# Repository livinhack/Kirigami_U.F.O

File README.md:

# Kirigami U.F.O.

Kirigami PCB v2 U.F.O.-Edition (inspired by timmit99)

### Since this PCB is a variation of my mod, you can find more helpful information at the link below!

https://github.com/livinhack/Kirigami_U.F.O/assets/91290219/f25b7a1e-6680-43ce-a2c9-361af66e349b

## [Back to Kirigami-PCB](https://github.com/livinhack/Kirigami-PCB)

# Change Log #

## V2.1:
 - The screw terminal moves ~ 3 mm further inwards

## V2:
 - Initial U.F.O. publication

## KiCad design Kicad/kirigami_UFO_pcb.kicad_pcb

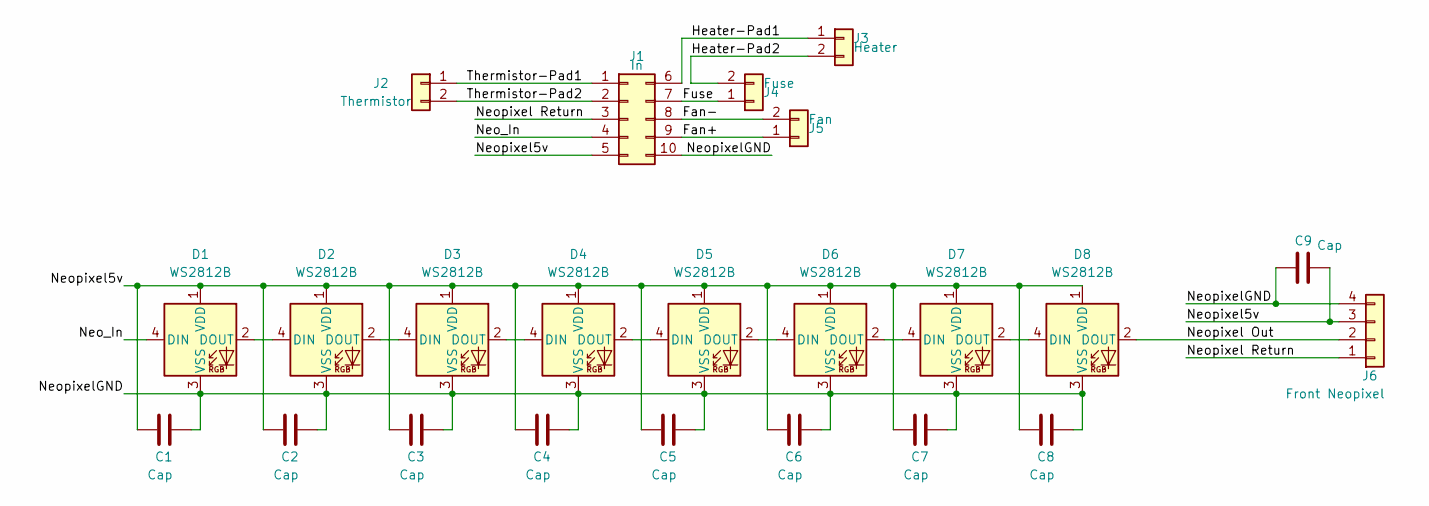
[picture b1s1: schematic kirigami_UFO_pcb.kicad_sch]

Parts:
C1, C2, C3, C4, C5, C6, C7, C8, C9: Cap; C_0805_2012Metric_Pad1.18x1.45mm_HandSolder
D1, D2, D3, D4, D5, D6, D7, D8: WS2812B; LED_WS2812B_PLCC4_5.0x5.0mm_P3.2mm
J1: In; Molex_Micro-Fit_3.0_43045-1000_2x05_P3.00mm_Horizontal
J2: Thermistor; JST_XH_B2B-XH-A_1x02_P2.50mm_Vertical
J3: Heater; METZ CONNECT USA Inc. - TERM BLK 2P SIDE ENT 5.08MM PCB
J4: Fuse; JST_XH_B2B-XH-A_1x02_P2.50mm_Vertical
J5: Fan; JST_XH_B2B-XH-A_1x02_P2.50mm_Vertical
J6: Front Neopixel; JST_XH_B4B-XH-A_1x04_P2.50mm_Vertical

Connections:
/Fan+: J1.9, J5.1
/Fan-: J1.8, J5.2
/Fuse: J1.7, J4.1
/Heater-Pad1: J1.6, J3.1
/Heater-Pad2: J3.2, J4.2
/Neo_In: D1.4 (DIN), J1.4
/Neopixel5v: C1.1, C2.1, C3.1, C4.1, C5.1, C6.1, C7.1, C8.1, C9.1, D1.1 (VDD), D2.1 (VDD), D3.1 (VDD), D4.1 (VDD), D5.1 (VDD), D6.1 (VDD), D7.1 (VDD), D8.1 (VDD), J1.5, J6.3
/Neopixel Out: D8.2 (DOUT), J6.2
/Neopixel Return: J1.3, J6.1
/NeopixelGND: C1.2, C2.2, C3.2, C4.2, C5.2, C6.2, C7.2, C8.2, C9.2, D1.3 (VSS), D2.3 (VSS), D3.3 (VSS), D4.3 (VSS), D5.3 (VSS), D6.3 (VSS), D7.3 (VSS), D8.3 (VSS), J1.10, J6.4
/Thermistor-Pad1: J1.1, J2.1
/Thermistor-Pad2: J1.2, J2.2
unnamed: D1.2 (DOUT), D2.4 (DIN)
unnamed: D2.2 (DOUT), D3.4 (DIN)
unnamed: D3.2 (DOUT), D4.4 (DIN)
unnamed: D4.2 (DOUT), D5.4 (DIN)
unnamed: D5.2 (DOUT), D6.4 (DIN)
unnamed: D6.2 (DOUT), D7.4 (DIN)
unnamed: D7.2 (DOUT), D8.4 (DIN)

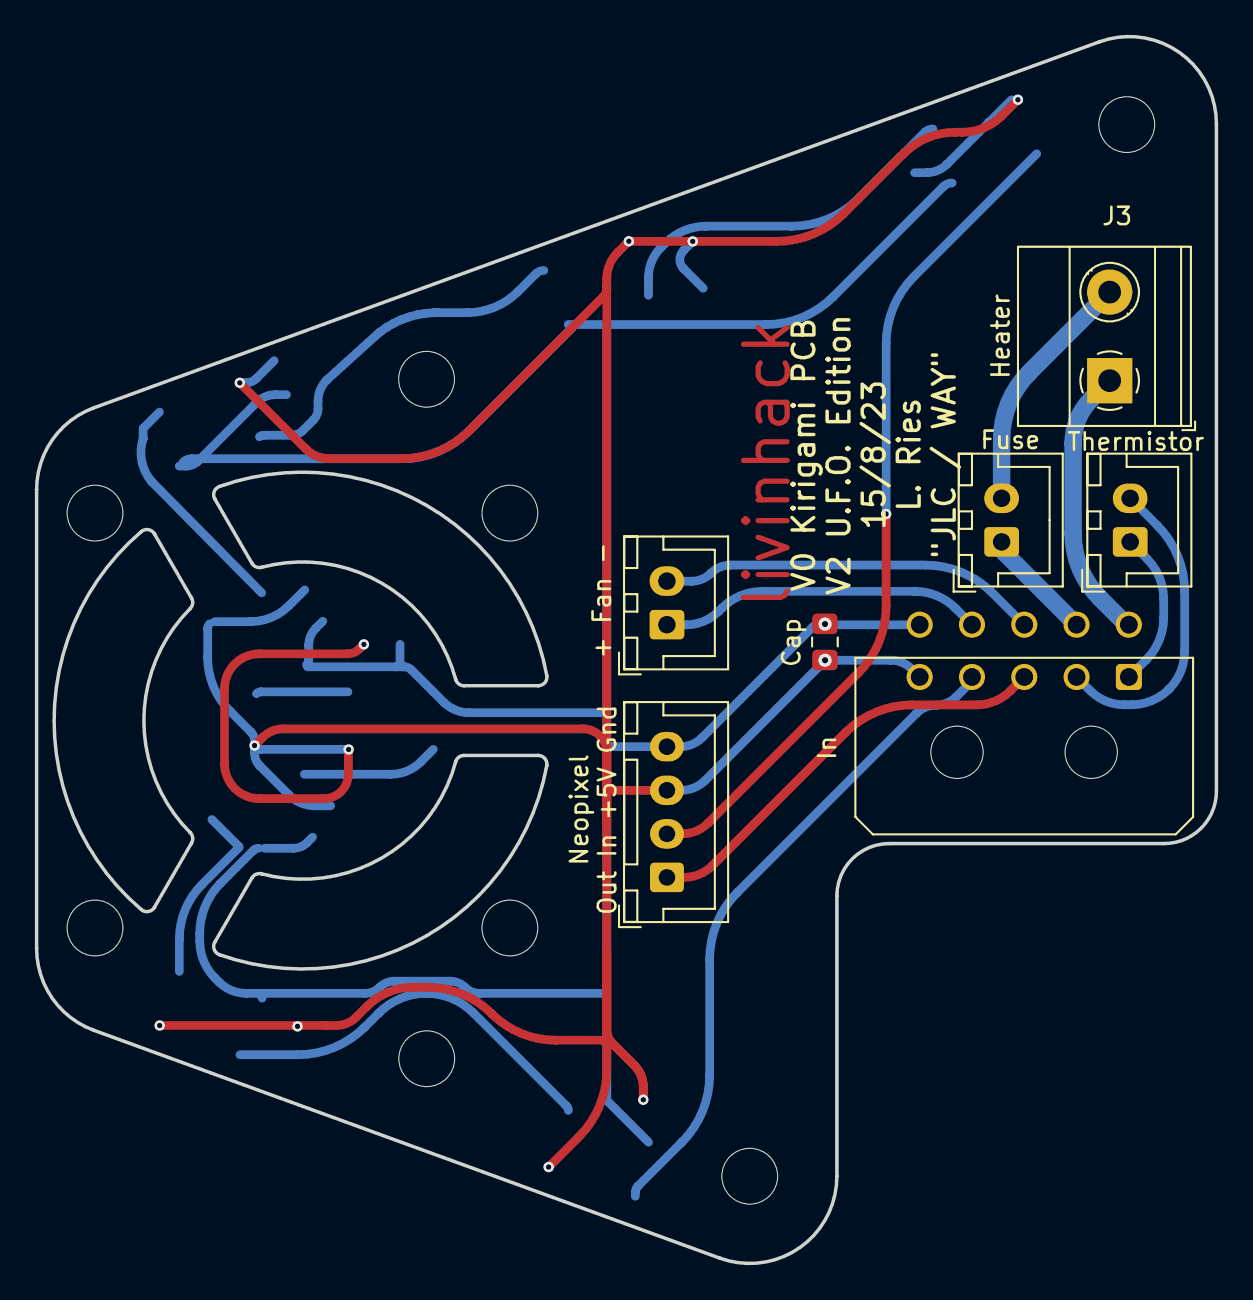
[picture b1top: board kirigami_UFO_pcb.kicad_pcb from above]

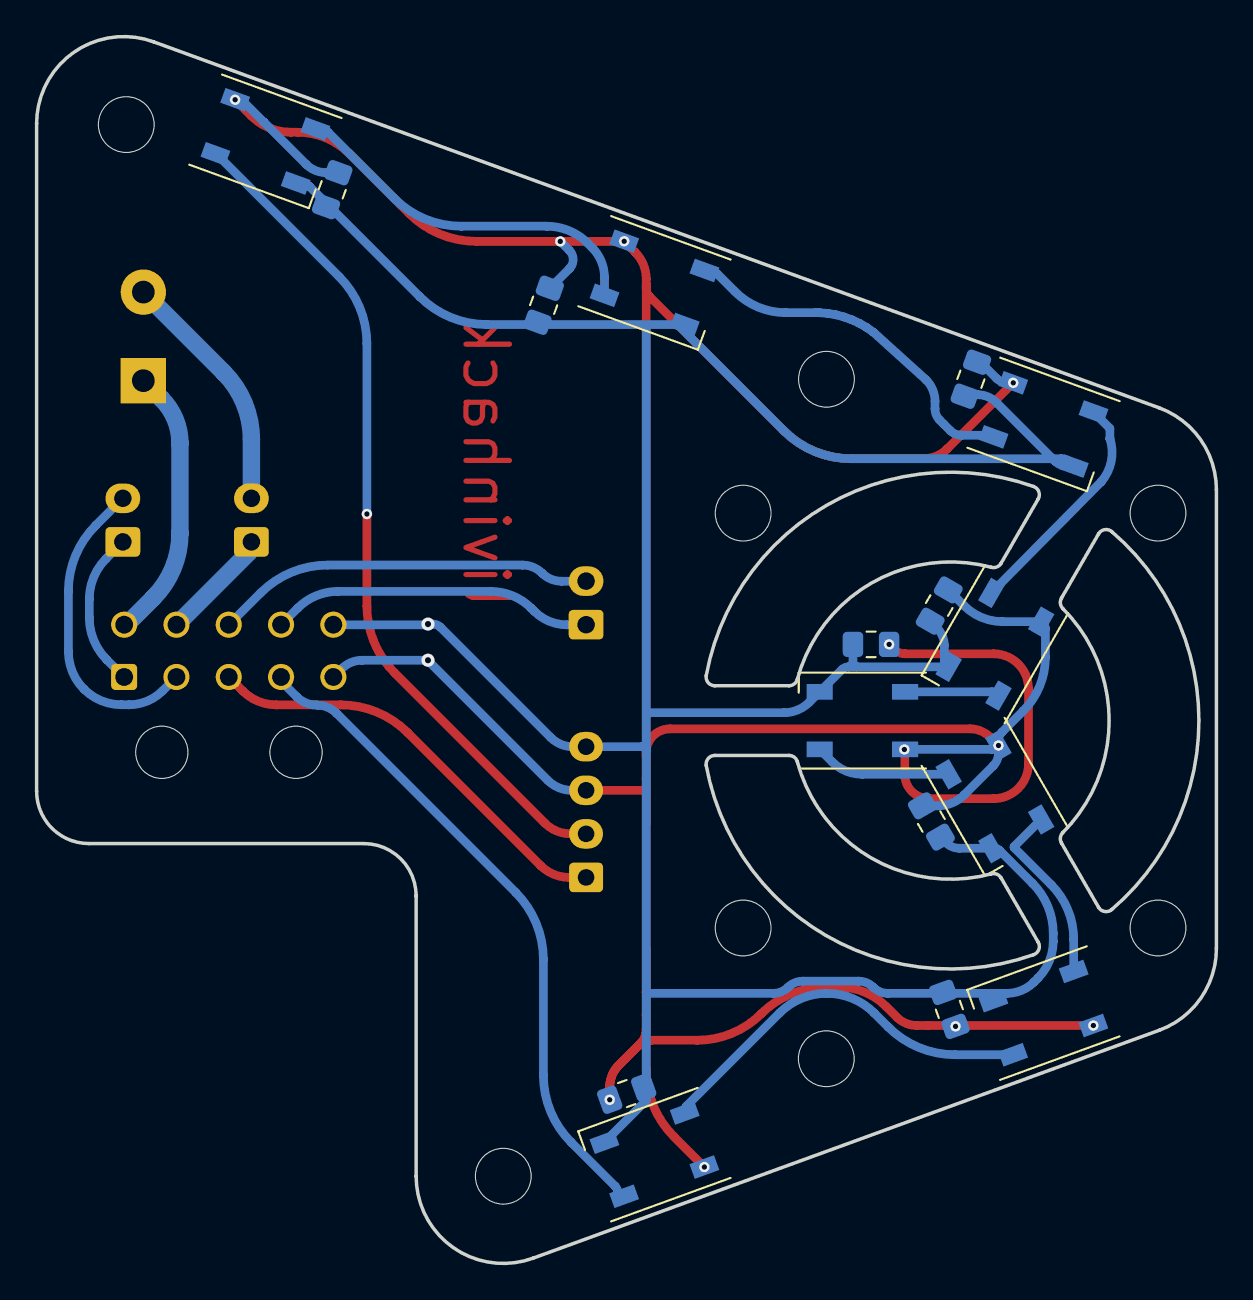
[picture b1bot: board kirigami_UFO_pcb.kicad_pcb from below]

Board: 2 copper layers, 67.7 x 70.4 mm, 31 parts (16 on the bottom side), 19 nets.

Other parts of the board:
H1, H2, H3, H4, H5, H6, H7, H8: MountingHole_3.2mm_M3

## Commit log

2023-08-08 chain order
2023-08-15 round tracks
2023-09-21 Schematic cleanup and organization
    A few changes to the schematic to aid in readability as well as simplifying signal flow.
2023-09-21 Delete ~kirigami_pcb.kicad_pcb.lck
    File removal
2024-04-08 Update README.md
    Hint to PCB repo
2024-04-11 Update
    add V2.1
